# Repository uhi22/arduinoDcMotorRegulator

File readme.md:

# Motor regulator for small DC motors

## Features:

* 12V input from power supply
* Motor voltage generation with PWM
* Measurement of motor voltage and motor current
* Constant speed control based on generated voltage
* Poti (pedal) input for target speed setting
* Thermo model of the motor, power reduction to prevent overheating

## Hardware

Arduino Nano, stepdown-converter with N-channel-FET.
KiCad schematics and board included

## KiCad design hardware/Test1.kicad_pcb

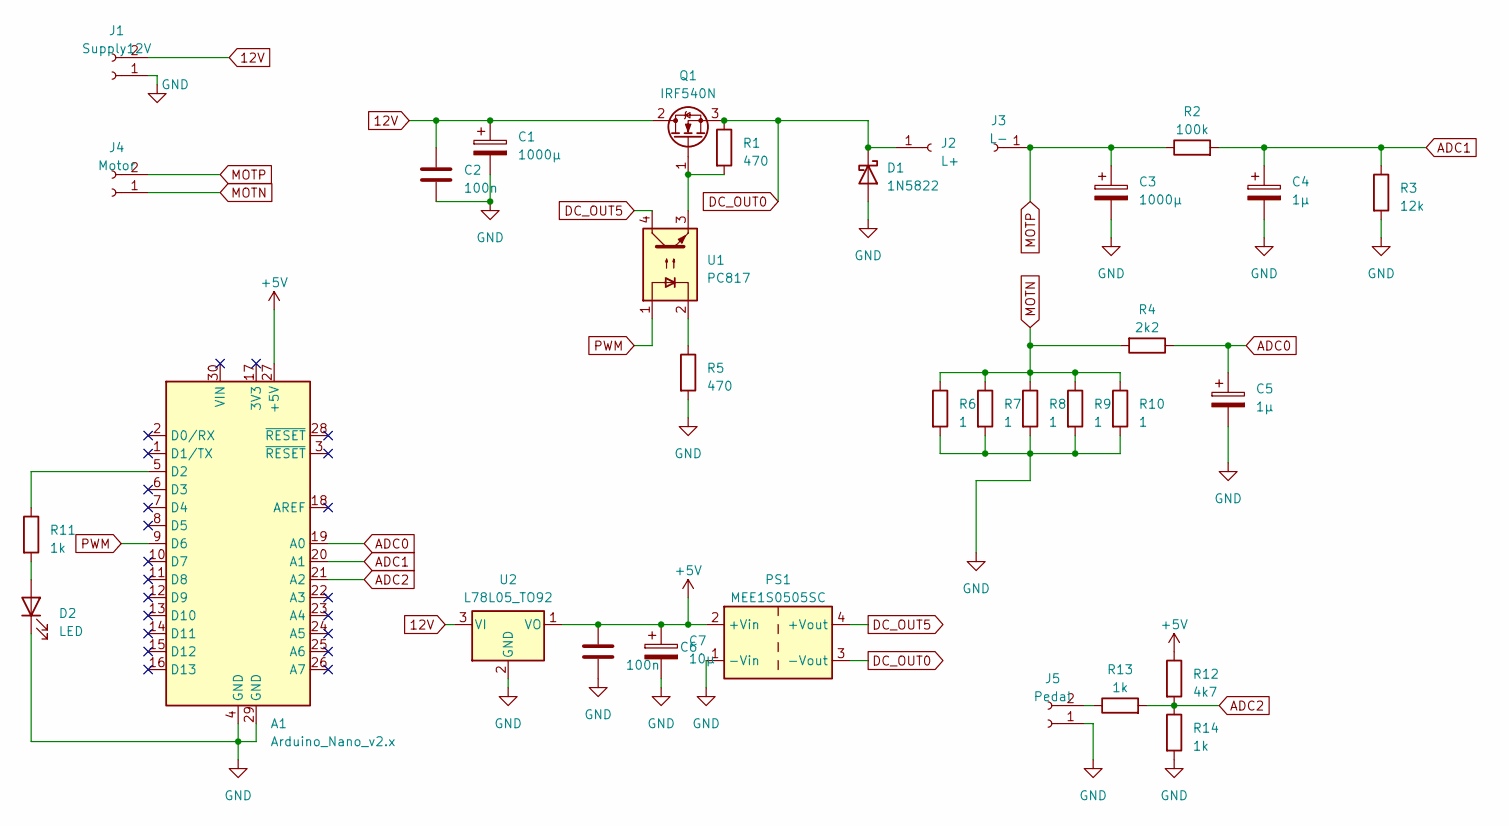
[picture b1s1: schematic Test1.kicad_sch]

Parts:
A1: Arduino_Nano_v2.x; Arduino_Nano
C1: 1000µ; C_Radial_D8.0mm_H7.0mm_P3.50mm
C2, C6: 100n; C_1206_3216Metric_Pad1.33x1.80mm_HandSolder
C3: 1000µ; CP_Radial_D10.0mm_P5.00mm
C4, C5: 1µ; CP_Radial_D6.3mm_P2.50mm
C7: 10µ; C_Radial_D5.0mm_H11.0mm_P2.00mm
D1: 1N5822; D_DO-201AD_P15.24mm_Horizontal
D2: LED; LED_D5.0mm_Clear
J1: Supply12V; SolderWire-0.75sqmm_1x02_P7mm_D1.25mm_OD3.5mm
J2: L+; SolderWire-0.75sqmm_1x01_D1.25mm_OD2.3mm
J3: L-; SolderWire-0.75sqmm_1x01_D1.25mm_OD2.3mm
J4: Motor; SolderWire-0.75sqmm_1x02_P7mm_D1.25mm_OD3.5mm
J5: Pedal; SolderWire-0.75sqmm_1x02_P7mm_D1.25mm_OD3.5mm
PS1: MEE1S0505SC; Converter_DCDC_Murata_MEE1SxxxxSC_THT
Q1: IRF540N; TO-220-3_Horizontal_TabDown
R1, R5: 470; R_Axial_DIN0309_L9.0mm_D3.2mm_P5.08mm_Vertical
R2: 100k; R_Axial_DIN0309_L9.0mm_D3.2mm_P5.08mm_Vertical
R3: 12k; R_Axial_DIN0309_L9.0mm_D3.2mm_P5.08mm_Vertical
R4: 2k2; R_Axial_DIN0309_L9.0mm_D3.2mm_P5.08mm_Vertical
R6, R7, R8, R9, R10: 1; R_Axial_DIN0309_L9.0mm_D3.2mm_P5.08mm_Vertical
R11, R13, R14: 1k; R_Axial_DIN0309_L9.0mm_D3.2mm_P5.08mm_Vertical
R12: 4k7; R_Axial_DIN0309_L9.0mm_D3.2mm_P5.08mm_Vertical
U1: PC817; DIP-4_W7.62mm
U2: L78L05_TO92; TO-92_Inline

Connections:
12V: C1.1, C2.1, J1.2, Q1.2 (D), U2.3 (VI)
+5V: A1.27 (+5V), C6.1, C7.1, PS1.2 (+Vin), R12.1, U2.1 (VO)
ADC0: A1.19 (A0), C5.1, R4.1
ADC1: A1.20 (A1), C4.1, R2.2, R3.1
ADC2: A1.21 (A2), R12.2, R13.2, R14.1
DC_OUT0: D1.1 (K), J2.1, PS1.3 (-Vout), Q1.3 (S), R1.1
DC_OUT5: PS1.4 (+Vout), U1.4
GND: A1.4 (GND), A1.29 (GND), C1.2, C2.2, C3.2, C4.2, C5.2, C6.2, C7.2, D1.2 (A), D2.1 (K), J1.1, J5.1, PS1.1 (-Vin), R3.2, R5.2, R6.2, R7.2, R8.2, R9.2, R10.2, R14.2, U2.2 (GND)
MOTN: J4.1, R4.2, R6.1, R7.1, R8.1, R9.1, R10.1
MOTP: C3.1, J3.1, J4.2, R2.1
unnamed: A1.5 (D2), R11.1
unnamed: D2.2 (A), R11.2
unnamed: J5.2, R13.1
unnamed: Q1.1 (G), R1.2, U1.3
unnamed: R5.1, U1.2
PWM: A1.9 (D6), U1.1

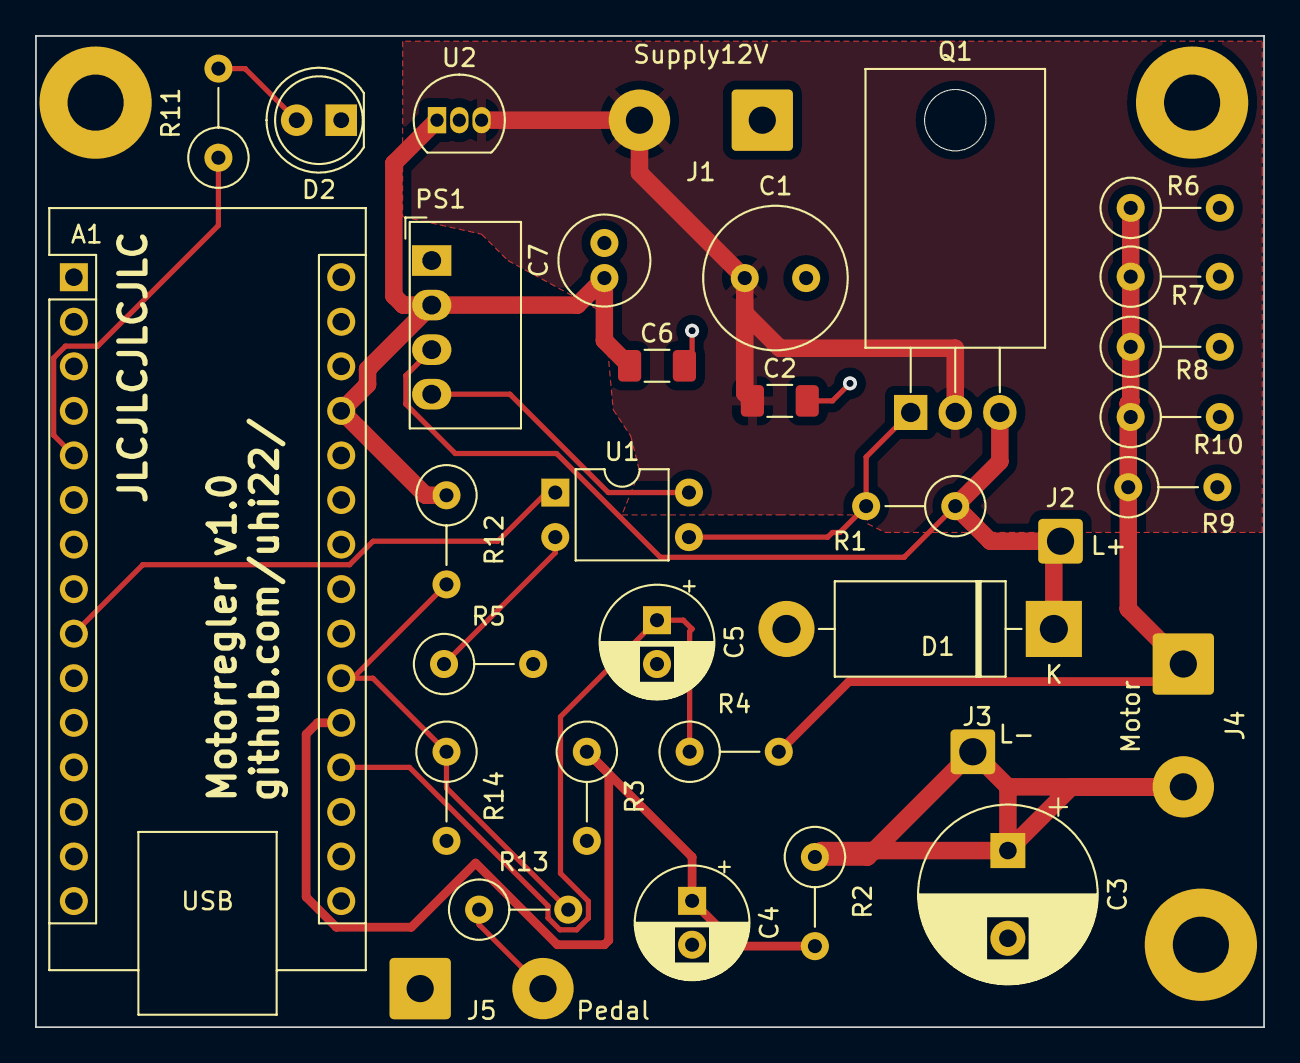
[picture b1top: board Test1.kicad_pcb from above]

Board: 2 copper layers, 70.0 x 56.5 mm, 33 parts (0 on the bottom side), 16 nets.
